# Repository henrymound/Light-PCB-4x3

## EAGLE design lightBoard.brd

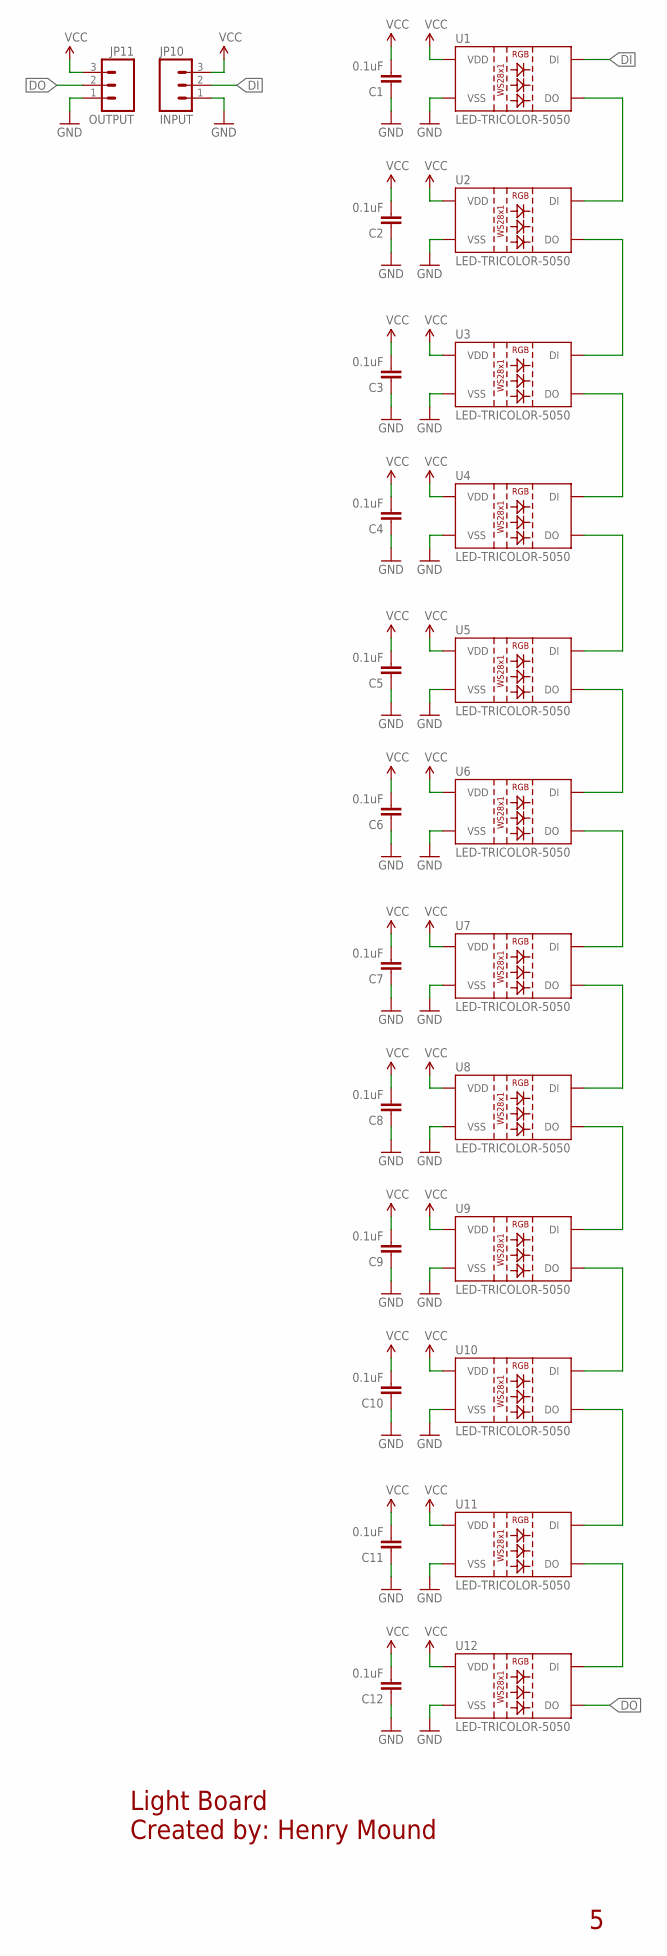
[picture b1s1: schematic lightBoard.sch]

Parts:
C1, C2, C3, C4, C5, C6, C7, C8, C9, C10, C11, C12: 0.1uF; 0603-CAP
JP10: INPUT; 1X03
JP11: OUTPUT; 1X03
U1, U2, U3, U4, U5, U6, U7, U8, U9, U10, U11, U12: LED-TRICOLOR-5050; LED-TRICOLOR-5050-IC

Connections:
DI: JP10.2, U1.2 (DI)
DO: JP11.2, U12.1 (DO)
GND: C1.1, C2.1, C3.1, C4.1, C5.1, C6.1, C7.1, C8.1, C9.1, C10.1, C11.1, C12.1, JP10.1, JP11.1, U1.6 (VSS), U2.6 (VSS), U3.6 (VSS), U4.6 (VSS), U5.6 (VSS), U6.6 (VSS), U7.6 (VSS), U8.6 (VSS), U9.6 (VSS), U10.6 (VSS), U11.6 (VSS), U12.6 (VSS)
unnamed: U1.1 (DO), U2.2 (DI)
unnamed: U3.1 (DO), U4.2 (DI)
unnamed: U2.1 (DO), U3.2 (DI)
unnamed: U5.1 (DO), U6.2 (DI)
unnamed: U7.1 (DO), U8.2 (DI)
unnamed: U6.1 (DO), U7.2 (DI)
unnamed: U9.1 (DO), U10.2 (DI)
unnamed: U11.1 (DO), U12.2 (DI)
unnamed: U10.1 (DO), U11.2 (DI)
unnamed: U8.1 (DO), U9.2 (DI)
unnamed: U4.1 (DO), U5.2 (DI)
VCC: C1.2, C2.2, C3.2, C4.2, C5.2, C6.2, C7.2, C8.2, C9.2, C10.2, C11.2, C12.2, JP10.3, JP11.3, U1.3 (VDD), U1.5 (VDD), U2.3 (VDD), U2.5 (VDD), U3.3 (VDD), U3.5 (VDD), U4.3 (VDD), U4.5 (VDD), U5.3 (VDD), U5.5 (VDD), U6.3 (VDD), U6.5 (VDD), U7.3 (VDD), U7.5 (VDD), U8.3 (VDD), U8.5 (VDD), U9.3 (VDD), U9.5 (VDD), U10.3 (VDD), U10.5 (VDD), U11.3 (VDD), U11.5 (VDD), U12.3 (VDD), U12.5 (VDD)

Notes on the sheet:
Light Board Created by: Henry Mound

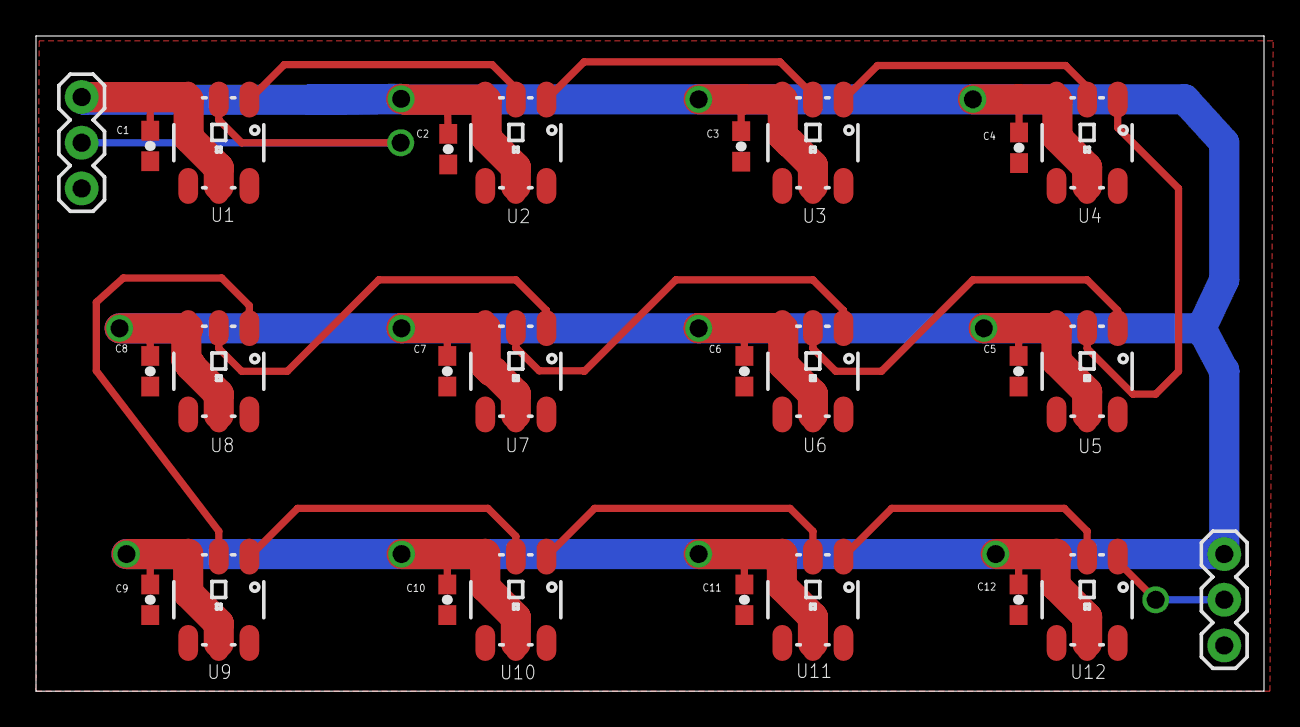
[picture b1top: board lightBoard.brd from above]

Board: 2 copper layers, 68.2 x 36.4 mm, 26 parts (0 on the bottom side), 15 nets.

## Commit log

2014-01-04 These are all the files for the Prototype PCB I have been making for the Quantum RGB LED Light
2014-01-06 Updated board with no 90 degree angles

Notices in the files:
parts and their libraries:
SparkFun-LED: Licensing: CC v3.0 Share-Alike You are welcome to use this library for commercial purposes.
